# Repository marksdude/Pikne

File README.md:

# Pikne
A modular and repairable power bank

Picture of rev 1.0 nonworking build
# Features:
- USB PD output up to 60W
- 0.91 inch OLED for status monitoring
- Attachable modules
- Repairable design
- 80WH capacity
- Based on the BQ25792 and TPS25751
- One USB-C output
# Modules:
- LED controller - Allows you to control LEDs with Home Assistant.
  - Features:
    - Up to 2.5A output
    - 5V output
    - Home Assistant integration
    - Power monitoring on each output
    - 2 monochrome outputs, 1 RGB output and 1 addressable LED output 
      - **Note:** RGB and the monochrome outputs can't be used simultaneously.
    - ESP32-C3 based

- Flashlight
  - Features:
    - 6600lm max brightness
      - **Note:** The LEDs probably won't be able to run at max brightness for very long.
    - PWM dimmable
    - STM32L011F3 based
# Coming modules
- LiPo charger - Allows you to charge up to 4S LiPos from your power bank
# How does it work?
Core functionality comes from the [TPS25751](https://www.ti.com/product/TPS25751) and [BQ25792](https://download.mikroe.com/documents/datasheets/BQ25792_datasheet.pdf) combination.  
  
The TPS25751 is a USB-C PD controller IC. It handles PD negotiations, manages the BQ25792 and also has integrated I2C control for the BQ25792, which simplified firmware development.  
  
The BQ25792 is a battery charger IC with support for USB-C PD output. It charges the battery and generates higher voltages (9V, 12V, 15V, 20V) for the USB C PD output. For 5V there is a separate regulator.
  
For example, if you connect a device you want to charge, first your device negotiates its required voltage and current with the TPS25751. Then the TPS25751 asks the BQ25792 to generate the requested voltage if it is above 5V. Once the correct voltage is available, the TPS25751 enables the output and your device starts charging.
  
An ATmega328P acts as the main controller. It monitors everything, handles faults, displays battery information and communicates with the modules.

The BMS is based on the BQ41Z50, a 2-4S battery manager IC. It has all the necessary protections needed for a lithium-ion battery pack and monitors its SoC (State of Charge). The ATmega328P requests battery information from the BMS over SMBus.

Modules can communicate with the power bank over UART through the pogo pins above the USB-C port. A connected module is idendified with an ID number sent by the module (1 for LED controller, 2 for Flashlight). The module can then request battery information or use the button on the power bank for additional control.
### LED controller
The LED controller is based on an ESP32-C3-WROOM-02U that is running ESPHome. There are 3 external MOSFETs that are used for the two monochrome outputs and one RGB output. An RGB output needs three MOSFETs, one for each color channel. Since there are only three, the monochrome outputs have to be connected together with two of the RGB channels. This is why the monochrome and RGB outputs can't be used simultaneously. INA219s are used for monitoring power draw of each output.

# Wiring
All of the smaller connectors are JST-ZH, while the battery connectors are JST-VH.  
The main PCB has 4 connectors. One goes to the pogo connector, two to the BMS and one is for programming.  

On the BMS two connectors go to the main PCB and two to the battery pack.  

The battery is connected in a 2S2P configuration. There are cutouts in the bottom of the battery holder for routing the wires and for the thermistors. BAT+ and BAT- connect to the BMS input, thermistors and the balance lead connect to the BMS battery sense connector.

The button has to be soldered to the main PCB. The pogo connector is connected to the main PCB.

### LED controller
Not much wiring to do here just connect the pogo connector to the PCB.

Output pinout:

# Firmware
Firmware is currently very limited. Version 0.1 has a basic menu to check some battery information, that's about it. It relies on the [ArduinoSMBus](https://github.com/osh-labs/ArduinoSMBus) library for communicating with the BMS and the [Adafruit_SSD1306](https://github.com/adafruit/adafruit_ssd1306) and [Adafruit GFX Library](https://github.com/adafruit/adafruit-gfx-library) libraries for drawing on the OLED. I plan to move away from these libraries in the future.  
  
There is still a lot left to be implemented.

# Why did I make this?
It all started because I was tired of changing the AA batteries in my mom's battery-powered lights. I wanted to make the process faster and less wasteful, so I thought it would be a good idea to design an easily removable, rechargeable battery pack for the lights and also integrate them with Home Assistant. The original idea was going to have 2 parts the battery pack and a controller board. They were supposed to be held together with magnets, connected with pogo pins and communicate over UART. Then I thought, why not turn the battery pack into a power bank so it could be used for things other than the lights? That's what I did. The idea of making the battery pack easily removable led me to make the power bank modular. That's how Pikne was born.

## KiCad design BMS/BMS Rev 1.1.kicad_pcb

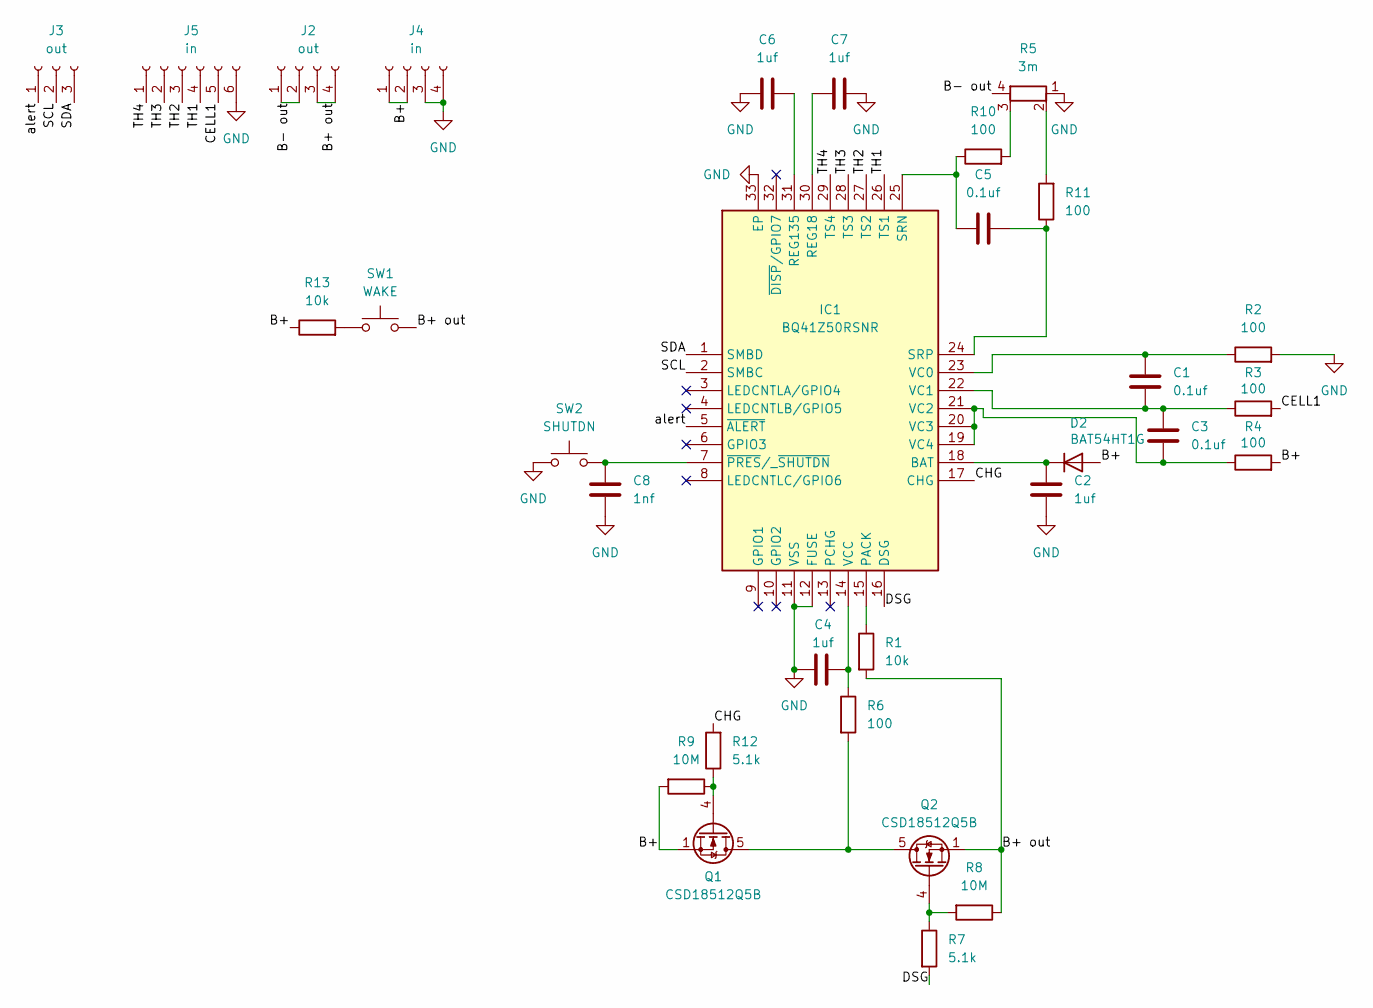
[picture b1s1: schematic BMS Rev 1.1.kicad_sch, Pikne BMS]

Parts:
C1, C3, C5: 0.1uf; C_0402_1005Metric
C2, C4, C6, C7: 1uf; C_0402_1005Metric
C8: 1nf; C_0402_1005Metric
D2: BAT54HT1G; D_SOD-323_HandSoldering
IC1: BQ41Z50RSNR; QFN40P400X400X80-33N-D; Manufacturer_Part_Number BQ41Z50RSNR
J2: out; JST_VH_S4P-VH_1x04_P3.96mm_Horizontal
J3: out; JST_ZH_B3B-ZR_1x03_P1.50mm_Vertical
J4: in; JST_VH_S4P-VH_1x04_P3.96mm_Horizontal
J5: in; JST_ZH_B6B-ZR_1x06_P1.50mm_Vertical
Q1, Q2: CSD18512Q5B; TDSON-8-1
R1, R13: 10k; R_0603_1608Metric
R2, R3, R4, R10, R11: 100; R_0402_1005Metric
R5: 3m; R_Shunt_Vishay_WSK2512_6332Metric_T2.21mm
R6: 100; R_0603_1608Metric
R7, R12: 5.1k; R_0402_1005Metric
R8, R9: 10M; R_0402_1005Metric
SW1: WAKE; SW_SPST_B3U-1000P
SW2: SHUTDN; SW_SPST_B3U-1000P

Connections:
/B+: D2.2 (A), J4.1, J4.2, Q1.1 (S), Q1.2 (S), Q1.3 (S), R4.2, R9.2, R13.1
/B+ out: J2.3, J2.4, Q2.1 (S), Q2.2 (S), Q2.3 (S), R1.2, R8.1, SW1.2
/B- out: J2.1, J2.2, R5.4
/CELL1: J5.5, R3.2
/CHG: IC1.17 (CHG), R12.2
/DSG: IC1.16 (DSG), R7.2
/SCL: IC1.2 (SMBC), J3.2
/SDA: IC1.1 (SMBD), J3.3
/TH1: IC1.26 (TS1), J5.4
/TH2: IC1.27 (TS2), J5.3
/TH3: IC1.28 (TS3), J5.2
/TH4: IC1.29 (TS4), J5.1
/alert: IC1.5 (~ALERT), J3.1
GND: C2.2, C4.1, C6.1, C7.2, C8.1, IC1.11 (VSS), IC1.12 (FUSE), IC1.33 (EP), J4.3, J4.4, J5.6, R2.2, R5.1, SW2.1
unnamed: C2.1, D2.1 (K), IC1.18 (BAT)
unnamed: IC1.15 (PACK), R1.1
unnamed: C7.1, IC1.30 (REG18)
unnamed: C6.2, IC1.31 (REG135)
unnamed: C5.1, IC1.25 (SRN), R10.1
unnamed: C5.2, IC1.24 (SRP), R11.1
unnamed: C1.1, IC1.23 (VC0), R2.1
unnamed: C1.2, C3.1, IC1.22 (VC1), R3.1
unnamed: C3.2, IC1.19 (VC4), IC1.20 (VC3), IC1.21 (VC2), R4.1
unnamed: C4.2, IC1.14 (VCC), R6.1
unnamed: C8.2, IC1.7 (~PRES/_~SHUTDN), SW2.2
unnamed: Q1.5 (D), Q2.5 (D), R6.2
unnamed: Q1.4 (G), R9.1, R12.1
unnamed: Q2.4 (G), R7.1, R8.2
unnamed: R5.3, R10.2
unnamed: R5.2, R11.2
unnamed: R13.2, SW1.1

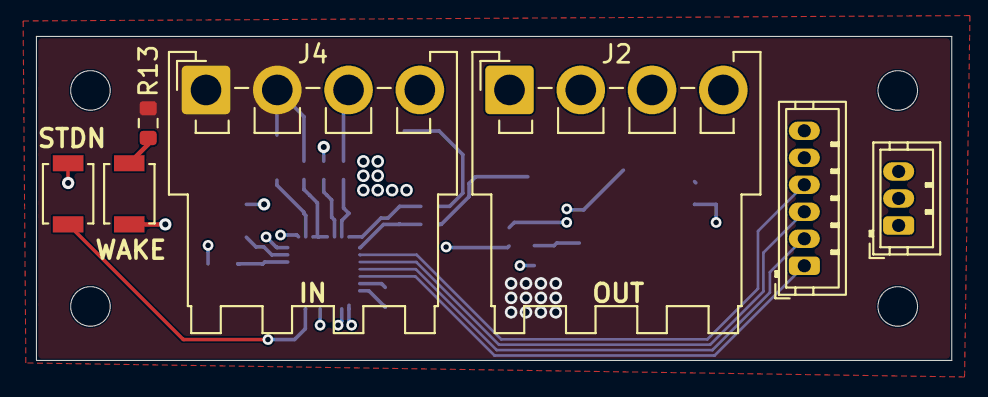
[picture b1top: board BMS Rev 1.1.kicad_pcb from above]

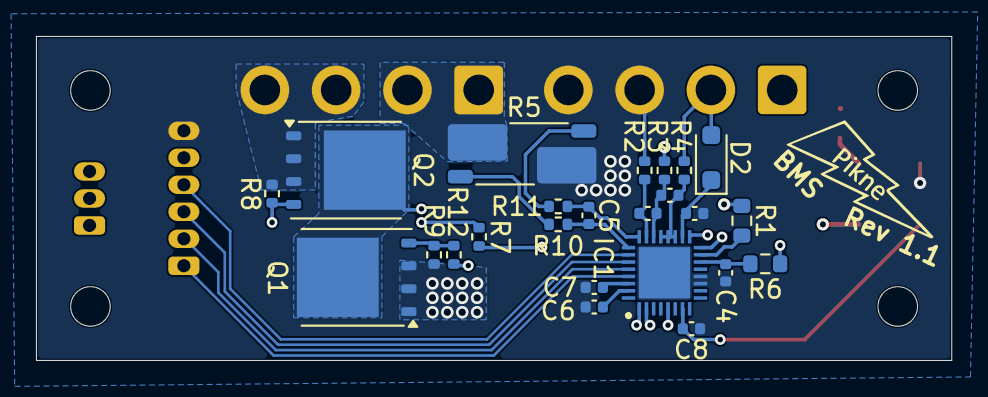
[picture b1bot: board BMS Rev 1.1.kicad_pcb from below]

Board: 4 copper layers, 50.9 x 18.0 mm, 31 parts (24 on the bottom side), 31 nets.

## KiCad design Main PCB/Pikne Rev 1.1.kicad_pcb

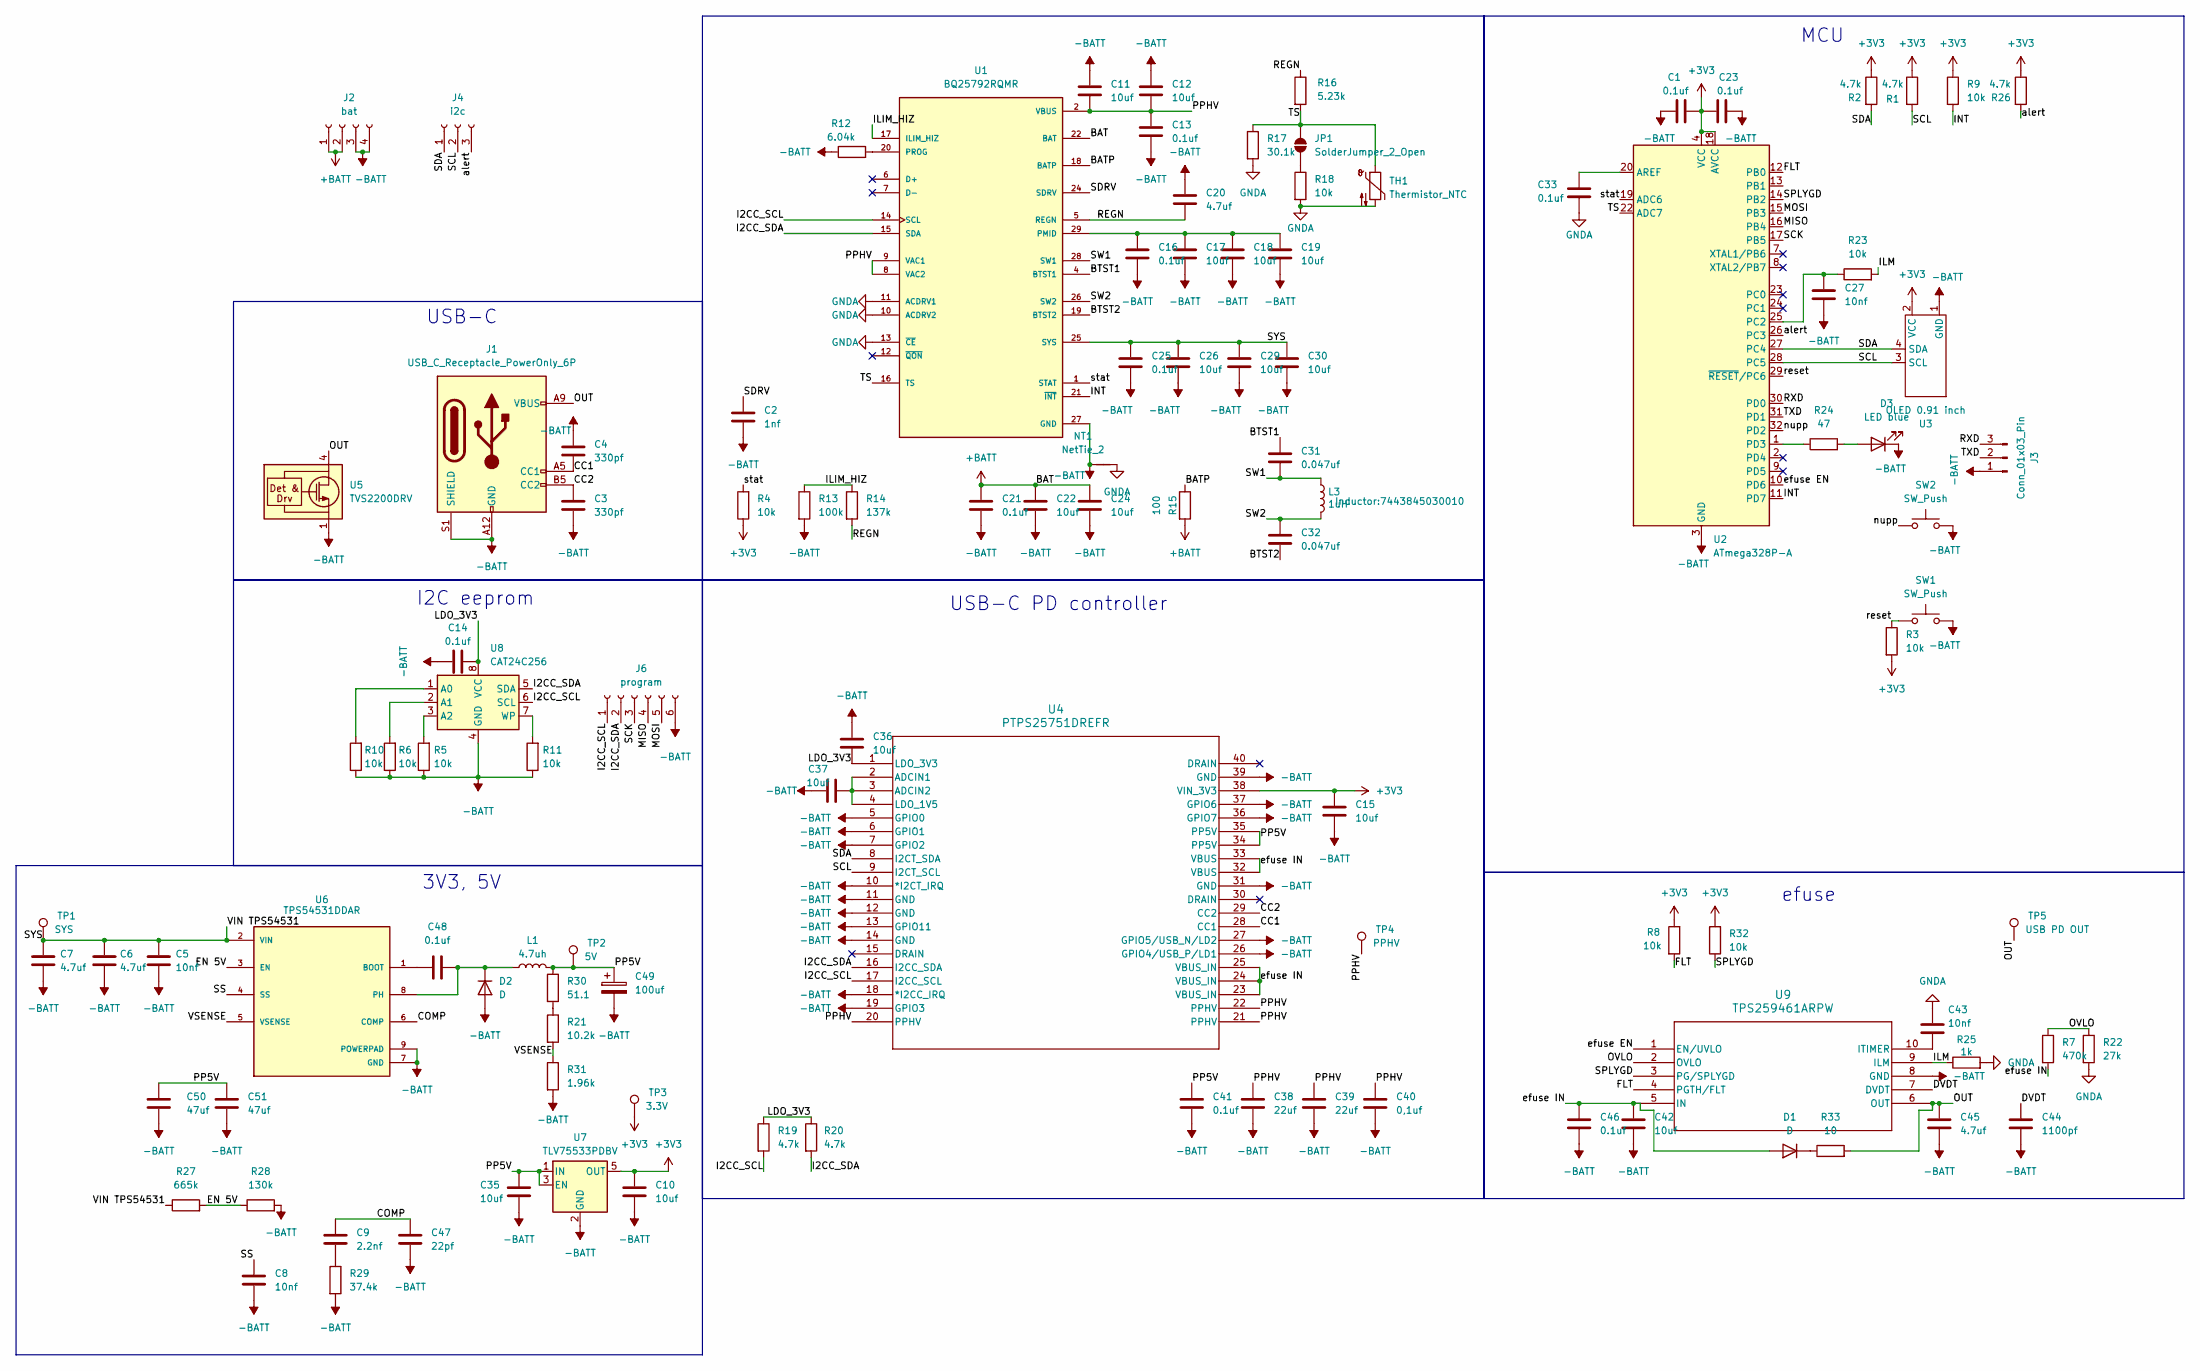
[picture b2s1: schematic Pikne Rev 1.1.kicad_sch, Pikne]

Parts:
C1, C13, C14, C16, C21, C23, C25, C33, C41, C46, C48: 0.1uf; C_0402_1005Metric
C2: 1nf; C_0402_1005Metric
C3, C4: 330pf; C_0402_1005Metric_Pad0.74x0.62mm_HandSolder
C5, C8, C27, C43: 10nf; C_0402_1005Metric
C6, C20: 4.7uf; C_0402_1005Metric
C7: 4.7uf; C_0402_1005Metric_Pad0.74x0.62mm_HandSolder
C9: 2.2nf; C_0402_1005Metric_Pad0.74x0.62mm_HandSolder
C10, C35: 10uf; C_0603_1608Metric_Pad1.08x0.95mm_HandSolder
C11, C12, C42: 10uf; C_0805_2012Metric
C15, C17, C18, C19, C22, C24, C26, C29, C30, C36, C37: 10uf; C_0603_1608Metric
C31, C32: 0.047uf; C_0402_1005Metric_Pad0.74x0.62mm_HandSolder
C38, C39: 22uf; C_0805_2012Metric
C40: 0,1uf; C_0402_1005Metric
C44: 1100pf; C_0402_1005Metric
C45: 4.7uf; C_0603_1608Metric
C47: 22pf; C_0402_1005Metric_Pad0.74x0.62mm_HandSolder
C49: 100uf; CP_Radial_D5.0mm_P2.50mm
C50, C51: 47uf; C_1210_3225Metric_Pad1.33x2.70mm_HandSolder
D1: D; D_SOD-323_HandSoldering
D2: D; D_SMC
D3: LED blue; LED_0603_1608Metric
J1: USB_C_Receptacle_PowerOnly_6P; USB_C_Receptacle_GCT_USB4125-xx-x-0190_6P_TopMnt_Horizontal
J2: bat; JST_VH_S4P-VH_1x04_P3.96mm_Horizontal
J3: Conn_01x03_Pin; JST_ZH_B3B-ZR_1x03_P1.50mm_Vertical
J4: i2c; JST_ZH_B3B-ZR_1x03_P1.50mm_Vertical
J6: program; JST_ZH_B6B-ZR_1x06_P1.50mm_Vertical
JP1: SolderJumper_2_Open; SolderJumper-2_P1.3mm_Open_Pad1.0x1.5mm
L1: 4.7uh; L_Bourns_SRP1038C_10.0x10.0mm
L3: 1uH; 7443845030010
NT1: NetTie_2; NetTie-2_THT_Pad0.3mm
R1, R2: 4.7k; R_0603_1608Metric_Pad0.98x0.95mm_HandSolder
R3, R18: 10k; R_0603_1608Metric_Pad0.98x0.95mm_HandSolder
R4, R8, R9, R32: 10k; R_0603_1608Metric
R5, R6, R10, R11: 10k; R_0402_1005Metric_Pad0.72x0.64mm_HandSolder
R7: 470k; R_0402_1005Metric
R12: 6.04k; R_0402_1005Metric
R13: 100k; R_0603_1608Metric
R14: 137k; R_0603_1608Metric
R15: 100; R_0402_1005Metric
R16: 5.23k; R_0603_1608Metric_Pad0.98x0.95mm_HandSolder
R17: 30.1k; R_0603_1608Metric_Pad0.98x0.95mm_HandSolder
R19, R20: 4.7k; R_0402_1005Metric
R21: 10.2k; R_0603_1608Metric
R22: 27k; R_0402_1005Metric
R23: 10k; R_0402_1005Metric
R24: 47; R_0603_1608Metric
R25: 1k; R_0402_1005Metric
R26: 4.7k; R_0603_1608Metric
R27: 665k; R_0603_1608Metric_Pad0.98x0.95mm_HandSolder
R28: 130k; R_0603_1608Metric_Pad0.98x0.95mm_HandSolder
R29: 37.4k; R_0402_1005Metric_Pad0.72x0.64mm_HandSolder
R30: 51.1; R_0603_1608Metric
R31: 1.96k; R_0603_1608Metric
R33: 10; R_0603_1608Metric
SW1, SW2: SW_Push; SW_SPST_B3U-1000P
TH1: Thermistor_NTC; ntc
TP1: SYS; TestPoint_Pad_D1.0mm
TP2: 5V; TestPoint_Pad_D1.0mm
TP3: 3.3V; TestPoint_Pad_D1.0mm
TP4: PPHV; TestPoint_Pad_D1.0mm
TP5: USB PD OUT; TestPoint_Pad_D1.0mm
U1: BQ25792RQMR; QFN40P400X400X100-29N; PARTREV 11/2019
U2: ATmega328P-A; TQFP-32_7x7mm_P0.8mm
U3: OLED 0.91 inch; SSD1306-0.91-OLED-4pin-128x32
U4: PTPS25751DREFR; WQFN38_REF_TEX
U5: TVS2200DRV; WSON-6-1EP_2x2mm_P0.65mm_EP1x1.6mm
U6: TPS54531DDAR; CONV_TPS54531DDAR; PARTREV A
U7: TLV75533PDBV; SOT-23-5
U8: CAT24C256; SOIC-8_3.9x4.9mm_P1.27mm
U9: TPS259461ARPW; VQFN10_RPW_TEX

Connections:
+3V3: C1.2, C10.1, C15.1, C23.1, R1.1, R2.1, R3.2, R4.1, R8.1, R9.1, R26.1, R32.2, TP3.1 (1_1), U2.4 (VCC), U2.6 (VCC), U2.18 (AVCC), U3.2 (VCC), U4.38 (VIN_3V3), U7.5 (OUT)
+BATT: C21.1, C22.1, C24.1, J2.1, J2.2, R15.2, U1.22 (BAT), U1.23 (BAT)
-BATT: C1.1, C2.1, C3.2, C4.1, C5.2, C6.2, C7.1, C8.2, C10.2, C11.1, C12.1, C13.1, C14.2, C15.2, C16.2, C17.2, C18.2, C19.2, C20.1, C21.2, C22.2, C23.2, C24.2, C25.2, C26.2, C27.2, C29.2, C30.2, C35.2, C36.2, C37.2, C38.2, C39.2, C40.2, C41.2, C42.2, C44.2, C45.2, C46.2, C47.2, C49.2, C50.2, C51.2, D2.2 (A), D3.1 (K), J1.A12 (GND), J1.B12 (GND), J1.S1 (SHIELD), J2.3, J2.4, J3.1, J6.6, NT1.1, R5.1, R6.1, R10.1, R11.1, R12.1, R13.2, R28.2, R29.2, R31.2, SW1.2, SW2.2, U1.27 (GND), U2.3 (GND), U2.5 (GND), U2.21 (GND), U3.1 (GND), U4.5 (GPIO0), U4.6 (GPIO1), U4.7 (GPIO2), U4.10 (*I2CT_IRQ), U4.11 (GND), U4.12 (GND), U4.13 (GPIO11), U4.14 (GND), U4.18 (*I2CC_IRQ), U4.19 (GPIO3), U4.26 (GPIO4/USB_P/LD1), U4.27 (GPIO5/USB_N/LD2), U4.31 (GND), U4.36 (GPIO7), U4.37 (GPIO6), U4.39 (GND), U5.1 (GND), U5.2 (GND), U5.3 (GND), U5.7 (GND), U6.7 (GND), U6.9 (POWERPAD), U6.10, U6.11, U6.12, U6.13, U6.14, U6.15, U7.2 (GND), U8.4 (GND), U9.8 (GND)
/BATP: R15.1, U1.18 (BATP)
/BTST1: C31.1, U1.4 (BTST1)
/BTST2: C32.2, U1.19 (BTST2)
/CC1: C4.2, J1.A5 (CC1), U4.28 (CC1)
/CC2: C3.1, J1.B5 (CC2), U4.29 (CC2)
/COMP: C9.1, C47.1, U6.6 (COMP)
/DVDT: C44.1, U9.7 (DVDT)
/EN 5V: R27.2, R28.1, U6.3 (EN)
/FLT: R8.2, U2.12 (PB0), U9.4 (PGTH/FLT)
/I2CC_SCL: J6.1, R19.2, U1.14 (SCL), U4.17 (I2CC_SCL), U8.6 (SCL)
/I2CC_SDA: J6.2, R20.2, U1.15 (SDA), U4.16 (I2CC_SDA), U8.5 (SDA)
/ILIM_HIZ: R13.1, R14.1, U1.17 (ILIM_HIZ)
/ILM: R23.2, R25.1, U9.9 (ILM)
/INT: R9.2, U1.21 (~INT), U2.11 (PD7)
/LDO_3V3: C14.1, C36.1, R19.1, R20.1, U4.1 (LDO_3V3), U8.8 (VCC)
/MISO: J6.4, U2.16 (PB4)
/MOSI: J6.5, U2.15 (PB3)
/OUT: C45.1, J1.A9 (VBUS), J1.B9 (VBUS), R33.2, TP5.1 (1_1), U5.4 (IN), U5.5 (IN), U5.6 (IN), U9.6 (OUT)
/OVLO: R7.1, R22.1, U9.2 (OVLO)
/PP5V: C35.1, C41.1, C49.1, C50.1, C51.1, L1.2, R30.1, TP2.1 (1_1), U4.34 (PP5V), U4.35 (PP5V), U7.1 (IN), U7.3 (EN)
/REGN: C20.2, R14.2, R16.1, U1.5 (REGN)
/RXD: J3.3, U2.30 (PD0)
/SCK: J6.3, U2.17 (PB5)
/SCL: J4.2, R1.2, U2.28 (PC5), U3.3 (SCL), U4.9 (I2CT_SCL)
/SDA: J4.1, R2.2, U2.27 (PC4), U3.4 (SDA), U4.8 (I2CT_SDA)
/SDRV: C2.2, U1.24 (SDRV)
/SPLYGD: R32.1, U2.14 (PB2), U9.3 (PG/SPLYGD)
/SS: C8.1, U6.4 (SS)
/SW1: C31.2, L3.1, U1.28 (SW1)
/SW2: C32.1, L3.2, U1.26 (SW2)
/SYS: C5.1, C6.1, C7.2, C25.1, C26.1, C29.1, C30.1, R27.1, TP1.1 (1_1), U1.25 (SYS), U6.2 (VIN)
/TS: JP1.1 (A), R16.2, R17.1, TH1.1, U1.16 (TS), U2.22 (ADC7)
/TXD: J3.2, U2.31 (PD1)
/VSENSE: R21.2, R31.1, U6.5 (VSENSE)
/alert: J4.3, R26.2, U2.26 (PC3)
/efuse EN: U2.10 (PD6), U9.1 (EN/UVLO)
/efuse IN: C42.1, C46.1, D1.2 (A), R7.2, U4.23 (VBUS_IN), U4.24 (VBUS_IN), U4.25 (VBUS_IN), U4.32 (VBUS), U4.33 (VBUS), U9.5 (IN)
/nupp: SW2.1, U2.32 (PD2)
/reset: R3.1, SW1.1, U2.29 (~RESET/PC6)
/stat: R4.2, U1.1 (STAT), U2.19 (ADC6)
GNDA: C33.2, C43.1, NT1.2, R17.2, R18.2, R22.2, R25.2, TH1.2, U1.10 (ACDRV2), U1.11 (ACDRV1), U1.13 (~CE)
unnamed: C9.2, R29.1
unnamed: D1.1 (K), R33.1
unnamed: C48.2, D2.1 (K), L1.1, U6.8 (PH)
unnamed: D3.2 (A), R24.2
unnamed: JP1.2 (B), R18.1
unnamed: R21.1, R30.2
unnamed: C16.1, C17.1, C18.1, C19.1, U1.29 (PMID)
unnamed: R12.2, U1.20 (PROG)
unnamed: C33.1, U2.20 (AREF)
unnamed: C27.1, R23.1, U2.25 (PC2)
unnamed: R24.1, U2.1 (PD3)
unnamed: C37.1, U4.2 (ADCIN1), U4.3 (ADCIN2), U4.4 (LDO_1V5)
unnamed: C48.1, U6.1 (BOOT)
unnamed: R10.2, U8.1 (A0)
unnamed: R6.2, U8.2 (A1)
unnamed: R5.2, U8.3 (A2)
unnamed: R11.2, U8.7 (WP)
unnamed: C43.2, U9.10 (ITIMER)
VBUS: C11.2, C12.2, C13.2, C38.1, C39.1, C40.1, TP4.1 (1_1), U1.2 (VBUS), U1.3 (VBUS), U1.8 (VAC2), U1.9 (VAC1), U4.20 (PPHV), U4.21 (PPHV), U4.22 (PPHV)

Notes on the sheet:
USB-C PD controller
MCU
3V3, 5V
I2C eeprom
efuse
USB-C

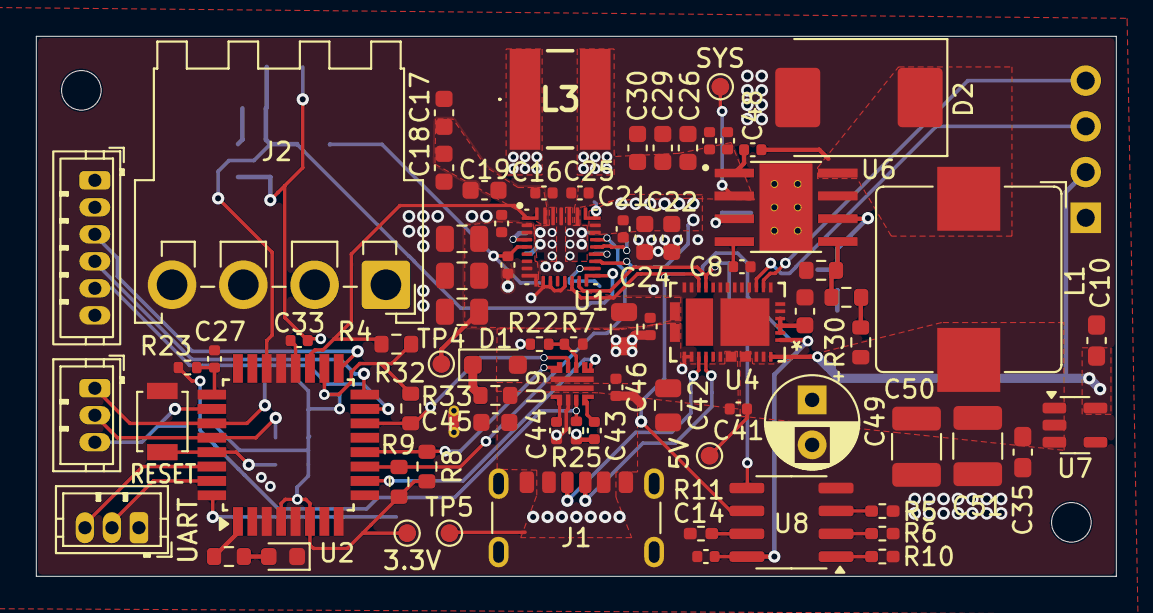
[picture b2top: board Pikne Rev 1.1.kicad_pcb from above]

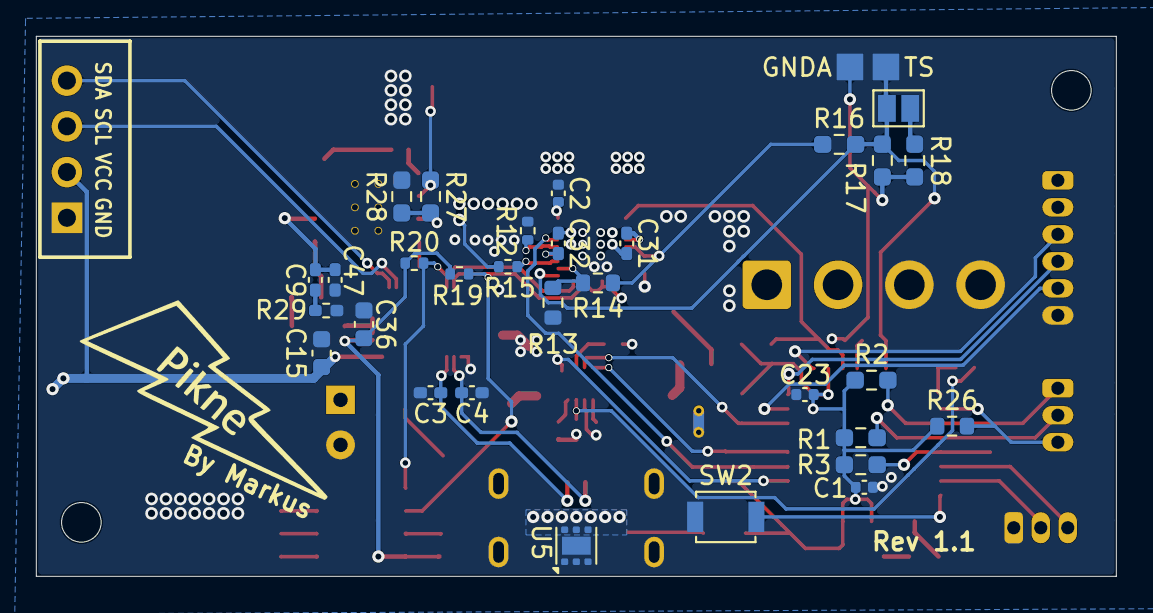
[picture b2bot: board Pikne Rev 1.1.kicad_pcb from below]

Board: 4 copper layers, 60.0 x 30.0 mm, 110 parts (32 on the bottom side), 63 nets.

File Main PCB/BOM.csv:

Id;Designator;Footprint;Quantity;Designation;Price (total) (EUR);Link;Part number
1;C1, C13, C14, C16, C21, C23, C25, C33, C41, C46, C48, C40;C_0402_1005Metric;12;0.1uf;0,18;https://www.mouser.ee/en/ProductDetail/Murata-Electronics/GR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;GRM155R62A104ME14D 
2;C2;C_0402_1005Metric;1;1nf;0,1;https://www.mouser.ee/en/ProductDetail/Walsin/0402B102M500CT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;0402B102M500CT
3;C3, C4;C_0402_1005Metric_Pad0.74x0.62mm_HandSolder;2;330pf;0,16;https://www.mouser.ee/en/ProductDetail/Samsung-Electro-Mecha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;CL05C331JB5NNNC 
4;C5, C8, C27, C43;C_0402_1005Metric;4;10nf;0,14;https://www.mouser.ee/en/ProductDetail/Murata-Electronics/GR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;GRT155R71E103KE01J 
5;C6, C20;C_0402_1005Metric;2;4.7uf;0,4;https://www.mouser.ee/en/ProductDetail/KYOCERA-AVX/KGM05CR51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;KGM05CR51C475MH 
6;C9;C_0402_1005Metric_Pad0.74x0.62mm_HandSolder;1;2.2nf;0,1;https://www.mouser.ee/en/ProductDetail/Murata-Electronics/GR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;GRM155R71H222KA01D 
7;C10, C35;C_0603_1608Metric_Pad1.08x0.95mm_HandSolder;2;10uf;0,21;https://www.mouser.ee/en/ProductDetail/Murata-Electronics/GR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;GRM188R61A106ME69D 
8;C11, C12, C42;C_0805_2012Metric;3;10uf;1,21;https://www.mouser.ee/en/ProductDetail/TDK/C2012X5R1V106K085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;C2012X5R1V106K085AC 
9;C15, C17, C18, C19, C22, C24, C26, C29, C30, C37, C36;C_0603_1608Metric;11;10uf;0,97;https://www.mouser.ee/en/ProductDetail/KYOCERA-AVX/0603YD106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;0603YD106KAT2A 
10;C31, C32;C_0402_1005Metric_Pad0.74x0.62mm_HandSolder;2;0.047uf;0,14;https://www.mouser.ee/en/ProductDetail/Murata-Electronics/GR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;GRM155R71H473ME14J 
11;;;;;;;
12;C38, C39;C_0805_2012Metric;2;22uf;1,1;https://www.mouser.ee/en/ProductDetail/TAIYO-YUDEN/MSAST21GB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;MSAST21GBB5226MTNC12
13;C40;;;;;;
14;C44;C_0402_1005Metric;1;1100pf;0,13;https://www.mouser.ee/en/ProductDetail/KEMET/C0402C112J4HACA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;C0402C112J4HACAUTO
15;C45;C_0603_1608Metric;1;4.7uf;0,27;https://www.mouser.ee/en/ProductDetail/Murata-Electronics/GR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;GRM188R6YA475ME15D
16;C47;C_0402_1005Metric_Pad0.74x0.62mm_HandSolder;1;22pf;0,11;https://www.mouser.ee/en/ProductDetail/Walsin/0402N220K500CT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;0402N220K500CT
17;C49;CP_Radial_D5.0mm_P2.50mm;1;100uf;;;
18;C50, C51;C_1210_3225Metric_Pad1.33x2.70mm_HandSolder;2;47uf;1,15;https://www.mouser.ee/en/ProductDetail/Samsung-Electro-Mecha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;CL32A476MOJNNNE
19;D1;D_SOD-323_HandSoldering;1;;0,23;https://www.mouser.ee/en/ProductDetail/Taiwan-Semiconductor/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;BAT42WSH RRG 
20;D2;D_SMC;1;;0,95;https://www.mouser.ee/en/ProductDetail/Comchip-Technology/CD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;CDBC540-G 
21;D3;LED_0603_1608Metric;1;LED blue;0,15;https://www.mouser.ee/en/ProductDetail/Wurth-Elektronik/1500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;150060BS75000 
22;J1;USB_C_Receptacle_GCT_USB4125-xx-x-0190_6P_TopMnt_Horizontal;1;USB_C_Receptacle_PowerOnly_6P;0,53;https://www.mouser.ee/ProductDetail/GCT/USB4125-GF-A?qs=KUoI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;USB4125-GF-A 
23;J2;JST_VH_S4P-VH_1x04_P3.96mm_Horizontal;1;JST VH S4P;0,26;https://www.mouser.ee/en/ProductDetail/JST-Commercial/S4P-VH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;S4P-VH(LF)(SN) 
24;J3, J4;JST_ZH_B3B-ZR_1x03_P1.50mm_Vertical;2;JST ZH B3B;0,41;https://www.mouser.ee/en/ProductDetail/JST-Commercial/B3B-ZR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;B3B-ZR-3.4(LF)(SN) 
25;;;;;;;
26;J6;JST_ZH_B6B-ZR_1x06_P1.50mm_Vertical;1;JST ZH B6B;0,28;https://www.mouser.ee/en/ProductDetail/JST-Commercial/B6B-ZR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;B6B-ZR-3.4(LF)(SN) 
27;L1;L_Bourns_SRP1038C_10.0x10.0mm;1;4.7uh;0,74;https://www.mouser.ee/en/ProductDetail/Bourns/SRP1038CC-4R7M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;SRP1038CC-4R7M 
28;L3;7443845030010;1;1uH;1,89;https://www.mouser.ee/en/ProductDetail/Wurth-Elektronik/7443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;7443845030010
29;R1, R2, R26;R_0603_1608Metric;3;4.7k;0,09;https://www.mouser.ee/en/ProductDetail/YAGEO/AC0603JR-074K7L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;AC0603JR-074K7L 
30;R3, R18, R4, R8, R9, R32;R_0603_1608Metric;6;10k;0,09;https://www.mouser.ee/en/ProductDetail/YAGEO/RT0603FRE1310KL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;RT0603FRE1310KL 
31;;;;;;;
32;R5, R6, R10, R11, R23;R_0402_1005Metric;5;10k;0,08;https://www.mouser.ee/en/ProductDetail/YAGEO/RC0402FR-0710KL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;RC0402FR-0710KL 
33;R7;R_0402_1005Metric;1;470k;0,09;https://www.mouser.ee/en/ProductDetail/YAGEO/RC0402FR-7D470K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;RC0402FR-7D470KL 
34;R12;R_0402_1005Metric;1;6.04k;0,09;https://www.mouser.ee/en/ProductDetail/YAGEO/RT0402FRE076K04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;RT0402FRE076K04L 
35;R13;R_0603_1608Metric;1;100k;0,09;https://www.mouser.ee/en/ProductDetail/YAGEO/RC0603FR-10100K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;RC0603FR-10100KL 
36;R14;R_0603_1608Metric;1;137k;0,09;https://www.mouser.ee/en/ProductDetail/YAGEO/AC0603FR-07137K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;AC0603FR-07137KL 
37;R15;R_0402_1005Metric;1;100 Ohm;0,08;https://www.mouser.ee/en/ProductDetail/YAGEO/AC0402FR-13100R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;AC0402FR-13100RL 
38;R16;R_0603_1608Metric_Pad0.98x0.95mm_HandSolder;1;5.23k;0,09;https://www.mouser.ee/en/ProductDetail/YAGEO/AC0603FR-075K23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;AC0603FR-075K23L 
39;R17;R_0603_1608Metric_Pad0.98x0.95mm_HandSolder;1;30.1k;0,1;https://www.mouser.ee/en/ProductDetail/Walsin/WR06X3012FTL?q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;WR06X3012FTL 
40;R19, R20;R_0402_1005Metric;2;4.7k;0,07;https://www.mouser.ee/en/ProductDetail/YAGEO/RC0402JR-104K7L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;RC0402JR-104K7L 
41;R21;R_0603_1608Metric;1;10.2k;0,09;https://www.mouser.ee/en/ProductDetail/YAGEO/RT0603FRE0710K2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;RT0603FRE0710K2L 
42;R22;R_0402_1005Metric;1;27k;0,09;https://www.mouser.ee/en/ProductDetail/Walsin/WR04X2702FTL?q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;WR04X2702FTL 
43;;;;;;;
44;R24;R_0603_1608Metric;1;47 Ohm;0,09;https://www.mouser.ee/en/ProductDetail/YAGEO/RT0603FRE0747RL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;RT0603FRE0747RL 
45;R25;R_0402_1005Metric;1;1k;0,09;https://www.mouser.ee/en/ProductDetail/YAGEO/RC0402FR-101KL?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;RC0402FR-101KL 
46;;;;;;;
47;R27;R_0603_1608Metric_Pad0.98x0.95mm_HandSolder;1;665k;0,09;https://www.mouser.ee/en/ProductDetail/SEI-Stackpole/RMCF060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;RMCF0603FT665K 
48;R28;R_0603_1608Metric_Pad0.98x0.95mm_HandSolder;1;130k;0,09;https://www.mouser.ee/en/ProductDetail/SEI-Stackpole/RMCF060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;RMCF0603FT130K 
49;R29;R_0402_1005Metric_Pad0.72x0.64mm_HandSolder;1;37.4k;0,08;https://www.mouser.ee/en/ProductDetail/YAGEO/RC0402FR-0737K4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;RC0402FR-0737K4L 
50;R30;R_0603_1608Metric;1;51.1;0,07;https://www.mouser.ee/en/ProductDetail/SEI-Stackpole/RMCF060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;RMCF0603FT51R1 
51;R31;R_0603_1608Metric;1;1.96k;0,09;https://www.mouser.ee/en/ProductDetail/SEI-Stackpole/RMCF060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;RMCF0603FT1K96 
52;R33;R_0603_1608Metric;1;10 Ohm;0,08;https://www.mouser.ee/en/ProductDetail/Walsin/WR06X100-JTL?q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;WR06X100 JTL 
53;SW1, SW2;SW_SPST_B3U-1000P;2;SW_Push;1,87;https://www.mouser.ee/en/ProductDetail/Omron-Electronics/B3U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;B3U-1000P 
54;TH1;ntc;1;NTC 10K;0,58;https://www.mouser.ee/en/ProductDetail/Semitec/103AT-2?qs=wg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;103AT-2 
55;TP1;TestPoint_Pad_D1.0mm;1;;;;
56;TP2;TestPoint_Pad_D1.0mm;1;;;;
57;TP3;TestPoint_Pad_D1.0mm;1;;;;
58;TP4;TestPoint_Pad_D1.0mm;1;;;;
59;TP5;TestPoint_Pad_D1.0mm;1;;;;
60;U1;QFN40P400X400X100-29N;1;BQ25792RQMR;6,33;https://www.mouser.ee/en/ProductDetail/Texas-Instruments/BQ2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;BQ25792RQMR 
61;U2;TQFP-32_7x7mm_P0.8mm;1;ATmega328P-A;2,29;https://www.mouser.ee/en/ProductDetail/Microchip-Technology/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;ATMEGA328P-AU 
62;U3;SSD1306-0.91-OLED-4pin-128x32;1;OLED 0.91 inch;2,64;https://www.aliexpress.com/item/1005008640108394.html;
63;U4;WQFN38_REF_TEX;1;TPS25751DREFR;2,57;https://www.mouser.ee/en/ProductDetail/Texas-Instruments/TPS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;TPS25751DREFR 
64;U5;WSON-6-1EP_2x2mm_P0.65mm_EP1x1.6mm;1;TVS2200DRV;0,93;https://www.mouser.ee/en/ProductDetail/Texas-Instruments/TVS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;TVS2200DRVR 
65;U6;CONV_TPS54531DDAR;1;TPS54531DDAR;1,95;https://www.mouser.ee/en/ProductDetail/Texas-Instruments/TPS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;TPS54531DDAR 
66;U7;SOT-23-5;1;TLV75533PDBV;0,38;https://www.mouser.ee/en/ProductDetail/Texas-Instruments/TLV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;TLV75533PDBVR 
67;U8;SOIC-8_3.9x4.9mm_P1.27mm;1;CAT24C256;0,63;https://www.mouser.ee/en/ProductDetail/onsemi/CAT24C256WI-GT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;CAT24C256WI-GT3 
68;U9;VQFN10_RPW_TEX;1;TPS259461ARPW;1,27;https://www.mouser.ee/en/ProductDetail/Texas-Instruments/TPS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;TPS259461ARPWR 
;;;;Total (EUR);35,07;;
;;;;Total (USD);40,69;;

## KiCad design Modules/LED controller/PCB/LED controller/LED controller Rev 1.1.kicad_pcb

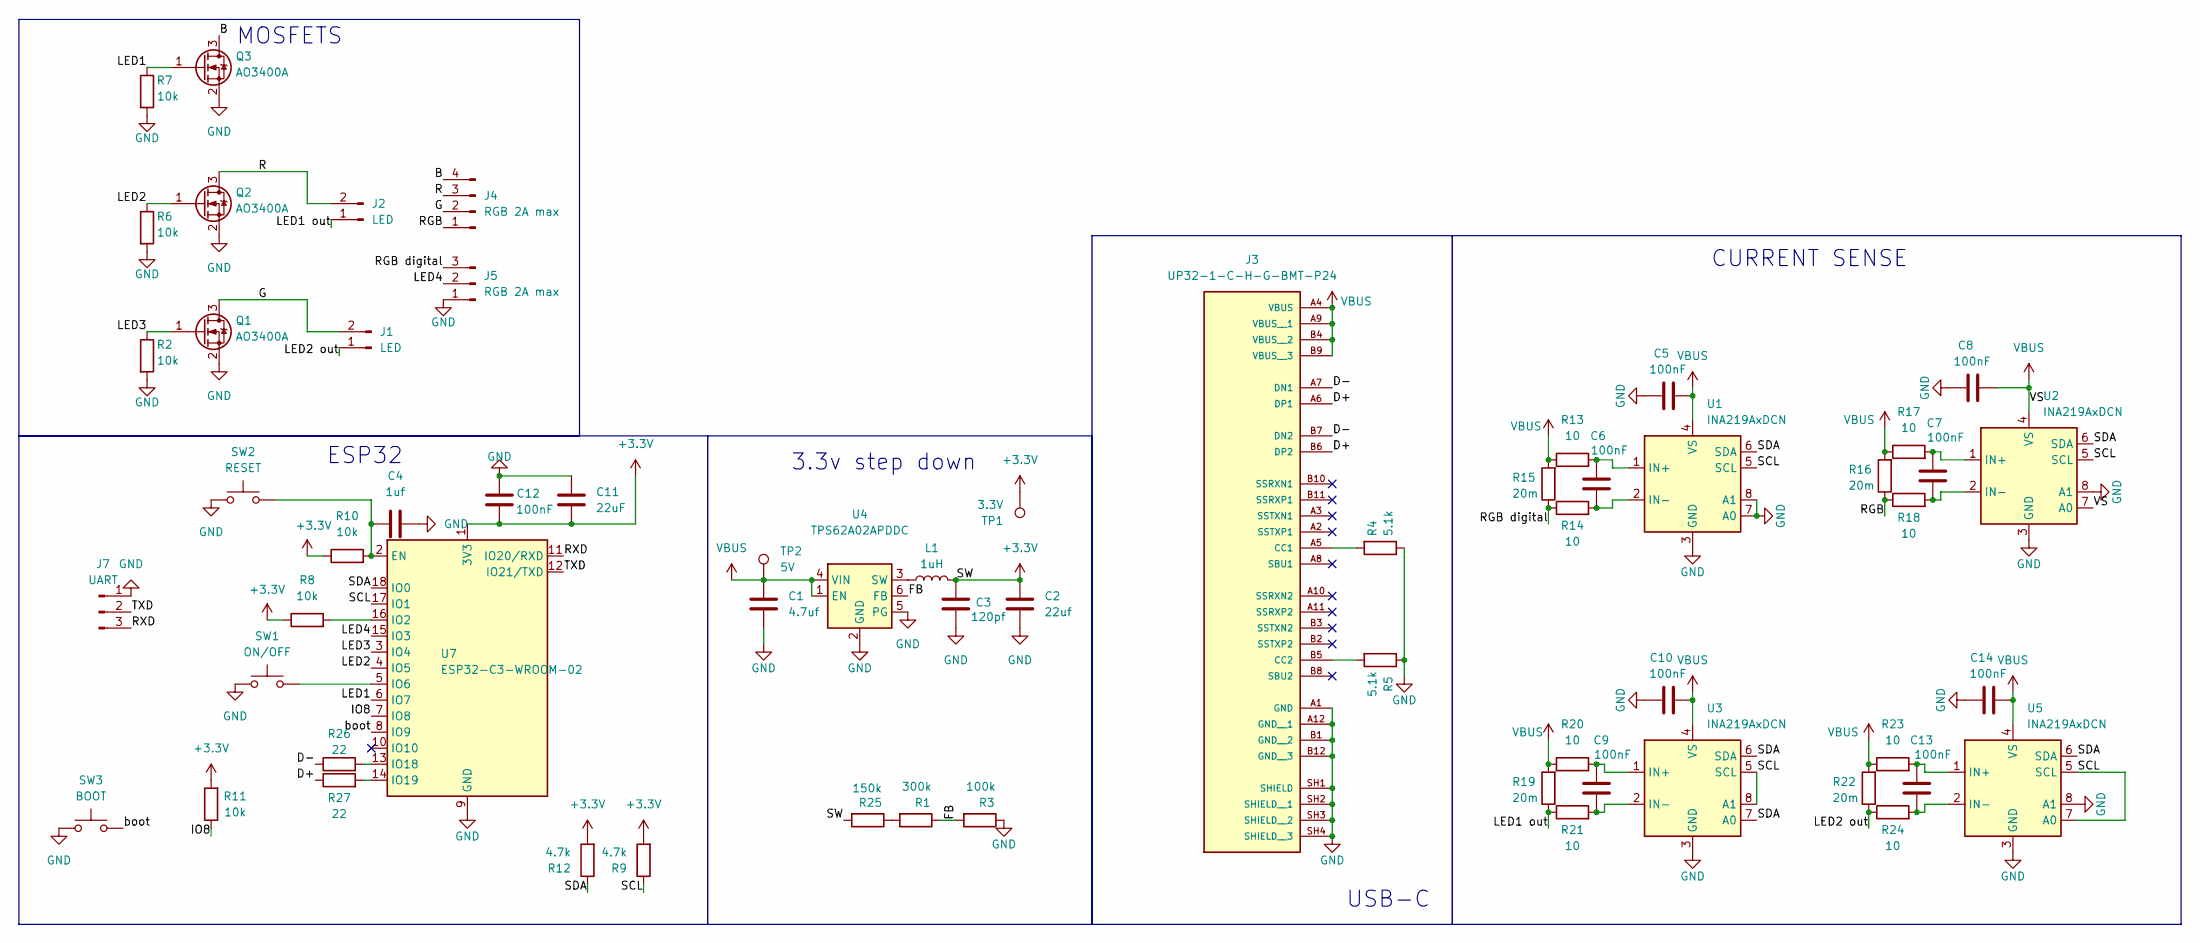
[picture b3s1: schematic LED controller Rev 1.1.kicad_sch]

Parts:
C1: 4.7uf; C_0603_1608Metric_Pad1.08x0.95mm_HandSolder
C2: 22uf; C_0603_1608Metric_Pad1.08x0.95mm_HandSolder
C3: 120pf; C_0402_1005Metric_Pad0.74x0.62mm_HandSolder
C4: 1uf; C_0603_1608Metric_Pad1.08x0.95mm_HandSolder
C5, C6, C7, C9, C10, C12, C13, C14: 100nF; C_0402_1005Metric_Pad0.74x0.62mm_HandSolder
C8: 100nF; C_0201_0603Metric_Pad0.64x0.40mm_HandSolder
C11: 22uF; C_0603_1608Metric_Pad1.08x0.95mm_HandSolder
J1, J2: LED; JST_XH_S2B-XH-A-1_1x02_P2.50mm_Horizontal
J3: UP32-1-C-H-G-BMT-P24; SAMESKY_UP32-1-C-H-G-BMT-P24; PARTREV 1.0
J4: RGB 2A max; JST_XH_S4B-XH-A-1_1x04_P2.50mm_Horizontal
J5: RGB 2A max; JST_XH_S3B-XH-A-1_1x03_P2.50mm_Horizontal
J7: UART; JST_ZH_B3B-ZR_1x03_P1.50mm_Vertical
L1: 1uH; L_1008_2520Metric_Pad1.43x2.20mm_HandSolder
Q1, Q2, Q3: AO3400A; SOT-23
R1: 300k; R_0402_1005Metric_Pad0.72x0.64mm_HandSolder
R2, R6, R7, R8, R10, R11: 10k; R_0603_1608Metric_Pad0.98x0.95mm_HandSolder
R3: 100k; R_0603_1608Metric_Pad0.98x0.95mm_HandSolder
R4, R5: 5.1k; R_0603_1608Metric_Pad0.98x0.95mm_HandSolder
R9, R12: 4.7k; R_0603_1608Metric_Pad0.98x0.95mm_HandSolder
R13, R14, R17, R18, R20, R21, R23, R24: 10; R_0402_1005Metric_Pad0.72x0.64mm_HandSolder
R15, R16, R19, R22: 20m; R_0805_2012Metric_Pad1.20x1.40mm_HandSolder
R25: 150k; R_0402_1005Metric_Pad0.72x0.64mm_HandSolder
R26, R27: 22; R_0402_1005Metric_Pad0.72x0.64mm_HandSolder
SW1: ON/OFF; SW_SPST_B3U-1000P
SW2: RESET; SW_SPST_B3U-1000P
SW3: BOOT; SW_SPST_B3U-1000P
TP1: 3.3V; TestPoint_Pad_D1.0mm
TP2: 5V; TestPoint_Pad_D1.0mm
U1, U2, U3, U5: INA219AxDCN; SOT-23-8
U4: TPS62A02APDDC; SOT-23-6
U7: ESP32-C3-WROOM-02; ESP32-C3-WROOM-02U

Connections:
+3.3V: C2.1, C3.1, C11.2, C12.2, L1.2, R8.1, R9.2, R10.1, R11.2, R12.2, R25.2, TP1.1 (1_1), U7.1 (3V3)
/B: J4.4, Q3.3 (D)
/D+: J3.A6 (DP1), J3.B6 (DP2), R27.1
/D-: J3.A7 (DN1), J3.B7 (DN2), R26.1
/FB: R1.1, R3.2, U4.6 (FB)
/G: J1.2, J4.2, Q1.3 (D)
/IO8: R11.1, U7.7 (IO8)
/LED1: Q3.1 (G), R7.1, U7.6 (IO7)
/LED1 out: J2.1, R19.1, R21.1
/LED2: Q2.1 (G), R6.1, U7.4 (IO5)
/LED2 out: J1.1, R22.1, R24.1
/LED3: Q1.1 (G), R2.1, U7.3 (IO4)
/LED4: J5.2, U7.15 (IO3)
/R: J2.2, J4.3, Q2.3 (D)
/RGB: J4.1, R16.1, R18.1
/RGB digital: J5.3, R14.1, R15.1
/RXD: J7.3, U7.11 (IO20/RXD)
/SCL: R9.1, U1.5 (SCL), U2.5 (SCL), U3.5 (SCL), U3.8 (A1), U5.5 (SCL), U5.7 (A0), U7.17 (IO1)
/SDA: R12.1, U1.6 (SDA), U2.6 (SDA), U3.6 (SDA), U3.7 (A0), U5.6 (SDA), U7.18 (IO0)
/TXD: J7.2, U7.12 (IO21/TXD)
/boot: SW3.2, U7.8 (IO9)
GND: C1.2, C2.2, C3.2, C4.1, C5.1, C8.1, C10.1, C11.1, C12.1, C14.1, J3.A1 (GND), J3.A12 (GND__1), J3.B1 (GND__2), J3.B12 (GND__3), J3.SH1 (SHIELD), J3.SH2 (SHIELD__1), J3.SH3 (SHIELD__2), J3.SH4 (SHIELD__3), J5.1, J7.1, Q1.2 (S), Q2.2 (S), Q3.2 (S), R2.2, R3.1, R4.1, R5.1, R6.2, R7.2, SW1.1, SW2.1, SW3.1, U1.3 (GND), U1.7 (A0), U1.8 (A1), U2.3 (GND), U2.8 (A1), U3.3 (GND), U4.2 (GND), U4.5 (PG), U5.3 (GND), U5.8 (A1), U7.9 (GND), U7.19 (GND)
unnamed: J3.A5 (CC1), R4.2
unnamed: J3.B5 (CC2), R5.2
unnamed: R1.2, R25.1
unnamed: C6.1, R13.2, U1.1 (IN+)
unnamed: C6.2, R14.2, U1.2 (IN-)
unnamed: C7.1, R17.2, U2.1 (IN+)
unnamed: C7.2, R18.2, U2.2 (IN-)
unnamed: C9.1, R20.2, U3.1 (IN+)
unnamed: C9.2, R21.2, U3.2 (IN-)
unnamed: L1.1, U4.3 (SW)
unnamed: C13.1, R23.2, U5.1 (IN+)
unnamed: C13.2, R24.2, U5.2 (IN-)
unnamed: C4.2, R10.2, SW2.2, U7.2 (EN)
unnamed: R8.2, U7.16 (IO2)
unnamed: SW1.2, U7.5 (IO6)
unnamed: R26.2, U7.13 (IO18)
unnamed: R27.2, U7.14 (IO19)
VBUS: C1.1, C5.2, C8.2, C10.2, C14.2, J3.A4 (VBUS), J3.A9 (VBUS__1), J3.B4 (VBUS__2), J3.B9 (VBUS__3), R13.1, R15.2, R16.2, R17.1, R19.2, R20.1, R22.2, R23.1, TP2.1 (1_1), U1.4 (VS), U2.4 (VS), U2.7 (A0), U3.4 (VS), U4.1 (EN), U4.4 (VIN), U5.4 (VS)

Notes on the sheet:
ESP32
USB-C
CURRENT SENSE
3.3v step down
MOSFETS
